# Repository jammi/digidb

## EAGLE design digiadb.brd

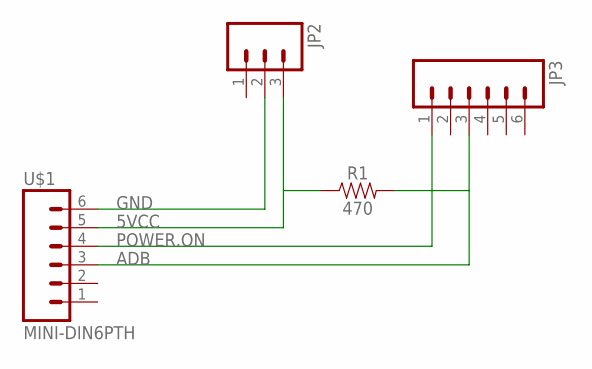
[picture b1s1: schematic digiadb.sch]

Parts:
JP2: M03PTH; 1X03
JP3: M06SIP; 1X06
R1: 470; 0603
U$1: MINI-DIN6PTH; MINI-DIN6

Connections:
5VCC: JP2.3, R1.1, U$1.5
ADB: JP3.3, R1.2, U$1.3
GND: JP2.2, U$1.6
POWER.ON: JP3.1, U$1.4

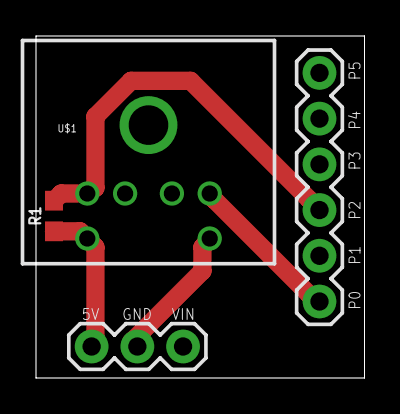
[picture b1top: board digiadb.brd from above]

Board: 2 copper layers, 18.2 x 19.0 mm, 4 parts (0 on the bottom side), 4 nets.

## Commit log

2018-05-15 Initial commit
    The state of the files are like in
    http://synack.net/svn/listing.php?repname=bbraun&path=%2Fdigidb%2F&#a8f68cdaaa142b796c2a115d5e46d61e8
    Further description in http://www.synack.net/~bbraun/morehid.html
2018-05-15 Ignored EAGLE temp files
2018-05-15 Implemented Caps Lock to Right Ctrl swap-around
    Also added the section key that's present on ISO keyboards
2018-05-15 Added EAGLE temp files to .gitignore
2018-05-15 added missing 470Ω pullup resistor from adb
2018-05-15 GPLv2
2018-05-16 Minor cleanup
    Tried to not change any functionality. Removed unused .inc files and unified formatting of the main file.
2018-05-16 more extra files removed
2018-05-16 Updated to most recent version of V-USB; WIP
    Some build issues need to be resolved
2018-05-16 Updated usbconfig
    Diffed and tweaked the updated usbdrv.h from the newest version, built and tested. Arduino had some issues regarding the .c file, which was resovled by using `extern "C"`
2018-05-16 Separated keymap into its own fine
    Tweaked the animation somewhat, and attempted some reconfiguration in order to trying to make the keyboard more responsive and less failprone. Still some occasional "i" or "F12" keys stuck and such.

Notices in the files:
parts and their libraries:
SparkFun: Licensing: CC v3.0 Share-Alike You are welcome to use this library for commercial purposes.
SparkFun-Connectors: Licensing: Creative Commons ShareAlike 4.0 International - https://creativecommons.org/licenses/by-sa/4.0
